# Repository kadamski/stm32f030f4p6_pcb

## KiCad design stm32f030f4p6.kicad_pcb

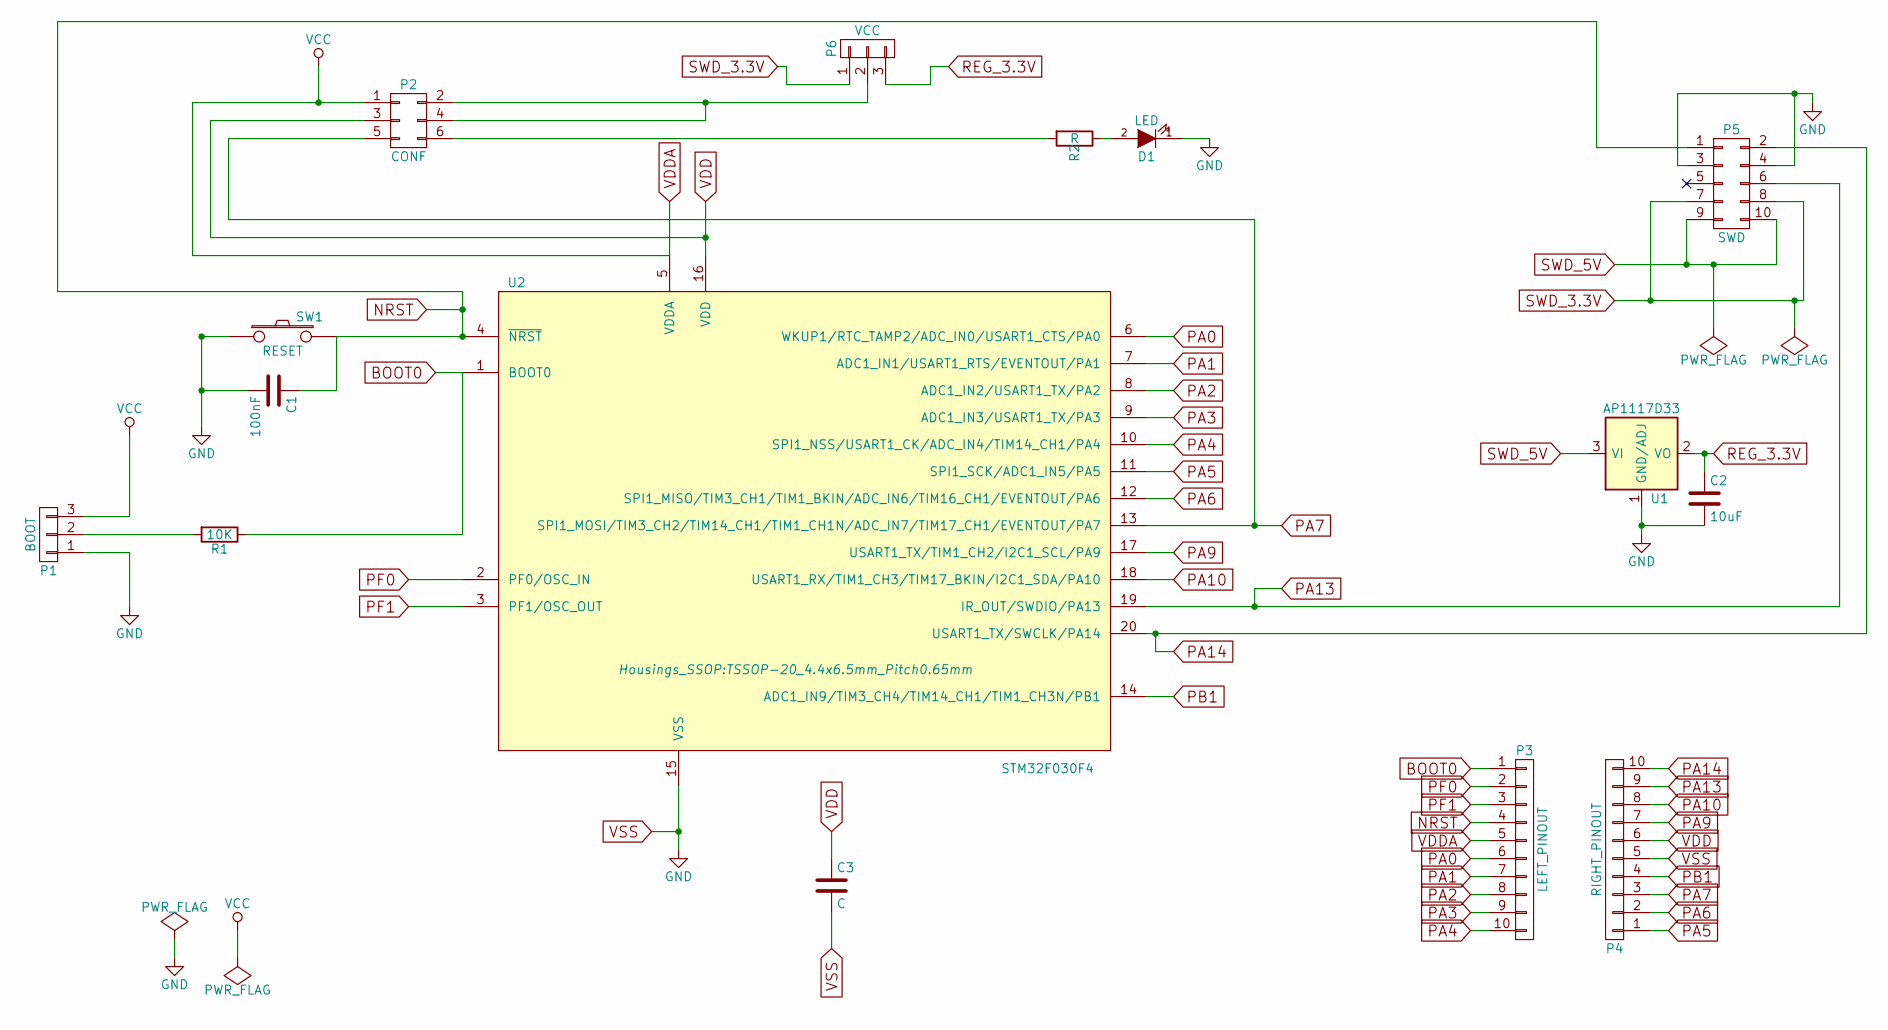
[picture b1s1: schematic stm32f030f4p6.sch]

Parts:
C1: 100nF; C_0805_HandSoldering
C2: 10uF; C_1206_HandSoldering
C3: C; C_0805_HandSoldering
D1: LED; LED-0805
P1: BOOT; Pin_Header_Straight_1x03
P2: CONF; Pin_Header_Straight_2x03
P3: LEFT_PINOUT; Pin_Header_Straight_1x10
P4: RIGHT_PINOUT; Pin_Header_Straight_1x10
P5: SWD; Pin_Header_Straight_2x05
P6: VCC; Pin_Header_Straight_1x03
R1: 10K; R_0805_HandSoldering
R2: R; R_0805_HandSoldering
SW1: RESET; SW_PUSH_SMALL
U1: AP1117D33; SOT-223
U2: STM32F030F4; TSSOP-20_4.4x6.5mm_Pitch0.65mm

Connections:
BOOT0: P3.1, R1.1, U2.1 (BOOT0)
NRST: C1.1, P3.4, P5.1, SW1.2, U2.4 (~NRST)
unnamed: D1.2 (A), R2.1
unnamed: P1.2, R1.2
unnamed: P2.2, P2.4, P6.2
unnamed: P2.6, R2.2
PA0: P3.6, U2.6 (WKUP1/RTC_TAMP2/ADC_IN0/USART1_CTS/PA0)
PA1: P3.7, U2.7 (ADC1_IN1/USART1_RTS/EVENTOUT/PA1)
PA2: P3.8, U2.8 (ADC1_IN2/USART1_TX/PA2)
PA3: P3.9, U2.9 (ADC1_IN3/USART1_TX/PA3)
PA4: P3.10, U2.10 (SPI1_NSS/USART1_CK/ADC_IN4/TIM14_CH1/PA4)
PA5: P4.1, U2.11 (SPI1_SCK/ADC1_IN5/PA5)
PA6: P4.2, U2.12 (SPI1_MISO/TIM3_CH1/TIM1_BKIN/ADC_IN6/TI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)
PA7: P2.5, P4.3, U2.13 (SPI1_MOSI/TIM3_CH2/TIM14_CH1/TIM1_CH1N/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)
PA9: P4.7, U2.17 (USART1_TX/TIM1_CH2/I2C1_SCL/PA9)
PA10: P4.8, U2.18 (USART1_RX/TIM1_CH3/TIM17_BKIN/I2C1_SDA/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)
PA13: P4.9, P5.6, U2.19 (IR_OUT/SWDIO/PA13)
PA14: P4.10, P5.2, U2.20 (USART1_TX/SWCLK/PA14)
PB1: P4.4, U2.14 (ADC1_IN9/TIM3_CH4/TIM14_CH1/TIM1_CH3N/P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)
PF0: P3.2, U2.2 (PF0/OSC_IN)
PF1: P3.3, U2.3 (PF1/OSC_OUT)
REG_3.3V: C2.1, P6.3, U1.2 (VO)
SWD_3.3V: P5.7, P5.8, P6.1
SWD_5V: P5.9, P5.10, U1.3 (VI)
VDD: C3.1, P2.3, P4.6, U2.16 (VDD)
VDDA: P1.3, P2.1, P3.5, U2.5 (VDDA)
VSS: C1.2, C2.2, C3.2, D1.1 (K), P1.1, P4.5, P5.3, P5.4, SW1.1, U1.1 (GND/ADJ), U2.15 (VSS)

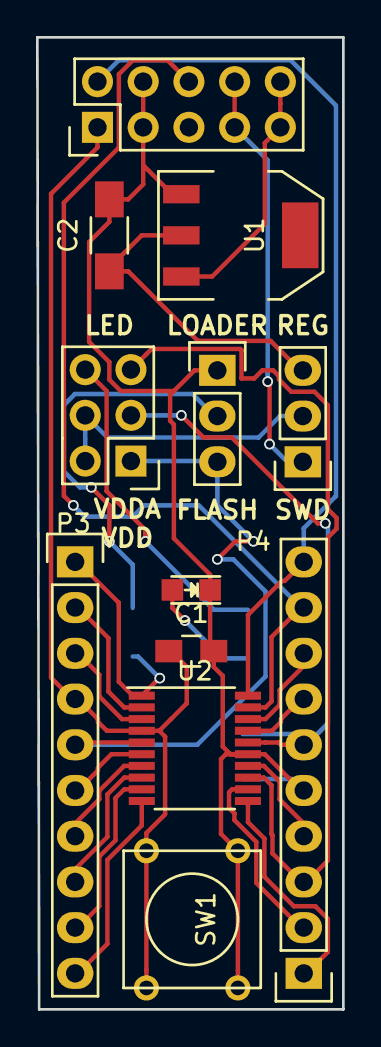
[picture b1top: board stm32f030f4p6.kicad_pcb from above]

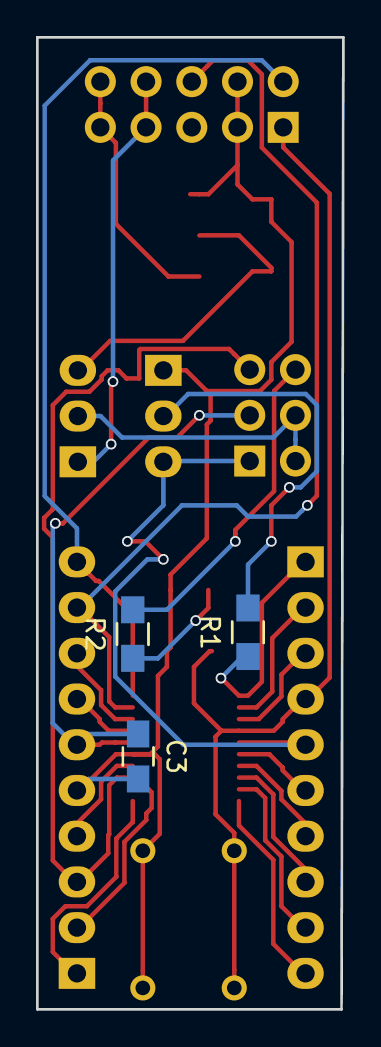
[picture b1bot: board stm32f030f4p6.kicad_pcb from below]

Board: 2 copper layers, 17.0 x 54.0 mm, 15 parts (3 on the bottom side), 27 nets.

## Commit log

2015-11-11 Init.
2015-11-11 Move library to LIB/
2015-11-11 Add cache.lib. Maybe usefull after all.
2015-11-22 shrinkify.
